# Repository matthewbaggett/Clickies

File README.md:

Clickies
========

Clickies - Whats the maximum fun you can have with a set of 1" square PCBs?

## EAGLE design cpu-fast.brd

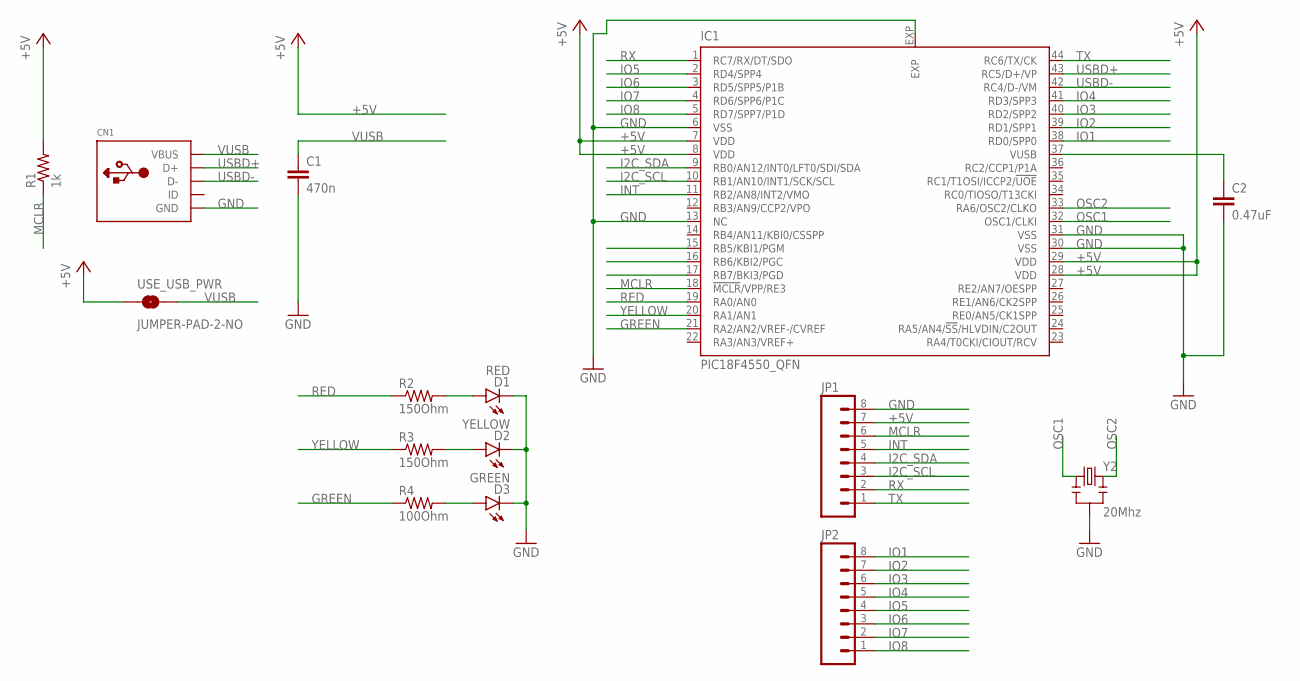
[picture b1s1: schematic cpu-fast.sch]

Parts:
C1: 470n; C0805K
C2: 0.47uF; 0603-CAP
CN1: USBMINIB; USB-MINIB
D1: RED; LED-0603
D2: YELLOW; LED-0603
D3: GREEN; LED-0603
IC1: PIC18F4550_QFN; QFN44ML8X8
JP1, JP2: M081X08; 1X08
R1: 1k; 0402-RES
R2, R3: 150Ohm; 0402-RES
R4: 100Ohm; 0402-RES
USE_USB_PWR: JUMPER-PAD-2-NO; PAD-JUMPER-2-NO_NO_SILK
Y2: 20Mhz; RESONATOR-SMD

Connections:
+5V: IC1.7 (VDD), IC1.8 (VDD), IC1.28 (VDD), IC1.29 (VDD), JP1.7, R1.2, USE_USB_PWR.1
GND: C1.2, C2.2, CN1.GND, D1.C, D2.C, D3.C, IC1.6 (VSS), IC1.13 (NC), IC1.30 (VSS), IC1.31 (VSS), IC1.EXP, JP1.8, Y2.2
GREEN: IC1.21 (RA2/AN2/VREF-/CVREF), R4.1
I2C_SCL: IC1.10 (RB1/AN10/INT1/SCK/SCL), JP1.3
I2C_SDA: IC1.9 (RB0/AN12/INT0/LFT0/SDI/SDA), JP1.4
INT: IC1.11 (RB2/AN8/INT2/VMO), JP1.5
IO1: IC1.38 (RD0/SPP0), JP2.8
IO2: IC1.39 (RD1/SPP1), JP2.7
IO3: IC1.40 (RD2/SPP2), JP2.6
IO4: IC1.41 (RD3/SPP3), JP2.5
IO5: IC1.2 (RD4/SPP4), JP2.4
IO6: IC1.3 (RD5/SPP5/P1B), JP2.3
IO7: IC1.4 (RD6/SPP6/P1C), JP2.2
IO8: IC1.5 (RD7/SPP7/P1D), JP2.1
MCLR: IC1.18 (!MCLR!/VPP/RE3), JP1.6, R1.1
unnamed: D1.A, R2.2
unnamed: D2.A, R3.2
unnamed: D3.A, R4.2
unnamed: C2.1, IC1.37 (VUSB)
OSC1: IC1.32 (OSC1/CLKI), Y2.1
OSC2: IC1.33 (RA6/OSC2/CLKO), Y2.3
RED: IC1.19 (RA0/AN0), R2.1
RX: IC1.1 (RC7/RX/DT/SDO), JP1.2
TX: IC1.44 (RC6/TX/CK), JP1.1
USBD+: CN1.D+, IC1.43 (RC5/D+/VP)
USBD-: CN1.D-, IC1.42 (RC4/D-/VM)
VUSB: C1.1, CN1.VBUS, USE_USB_PWR.2
YELLOW: IC1.20 (RA1/AN1), R3.1

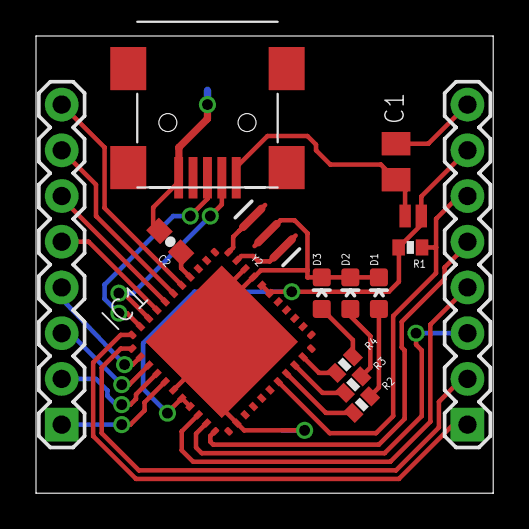
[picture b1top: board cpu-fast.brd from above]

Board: 2 copper layers, 25.4 x 25.4 mm, 15 parts (0 on the bottom side), 28 nets.

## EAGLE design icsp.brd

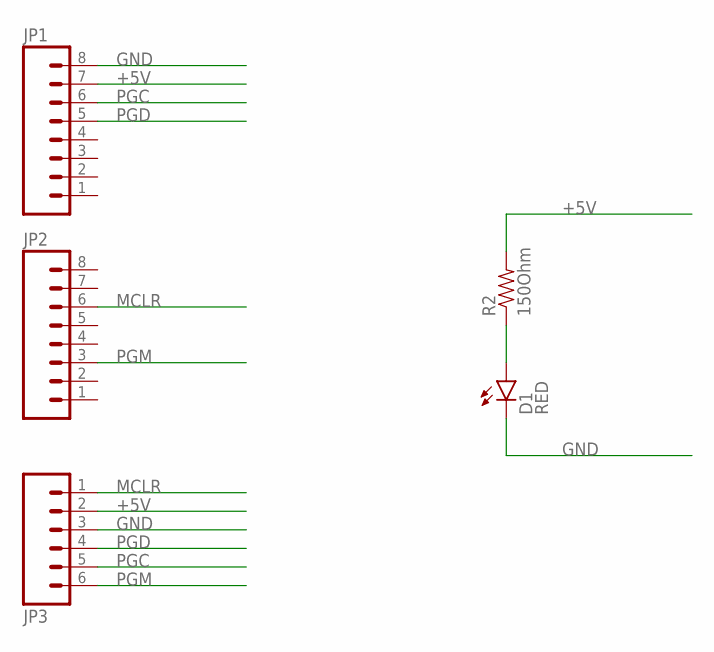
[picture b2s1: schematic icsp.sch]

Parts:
D1: RED; LED-0603
JP1, JP2: M081X08; 1X08
JP3: M06SIP_LOCK; 1X06-SIP_LOCK
R2: 150Ohm; 0402-RES

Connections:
+5V: JP1.7, JP3.2, R2.2
GND: D1.C, JP1.8, JP3.3
MCLR: JP2.6, JP3.1
unnamed: D1.A, R2.1
PGC: JP1.6, JP3.5
PGD: JP1.5, JP3.4
PGM: JP2.3, JP3.6

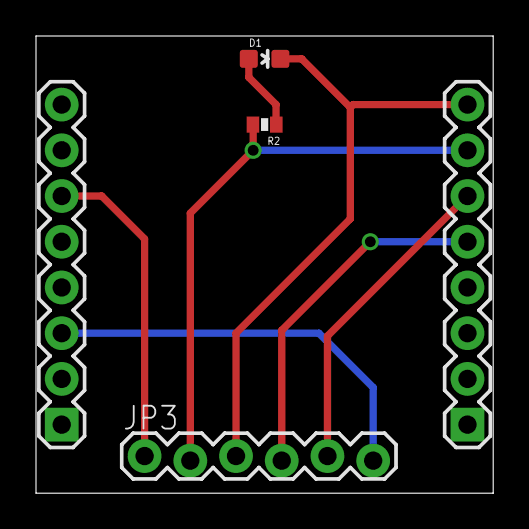
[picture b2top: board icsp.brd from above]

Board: 2 copper layers, 25.4 x 25.4 mm, 5 parts (0 on the bottom side), 7 nets.

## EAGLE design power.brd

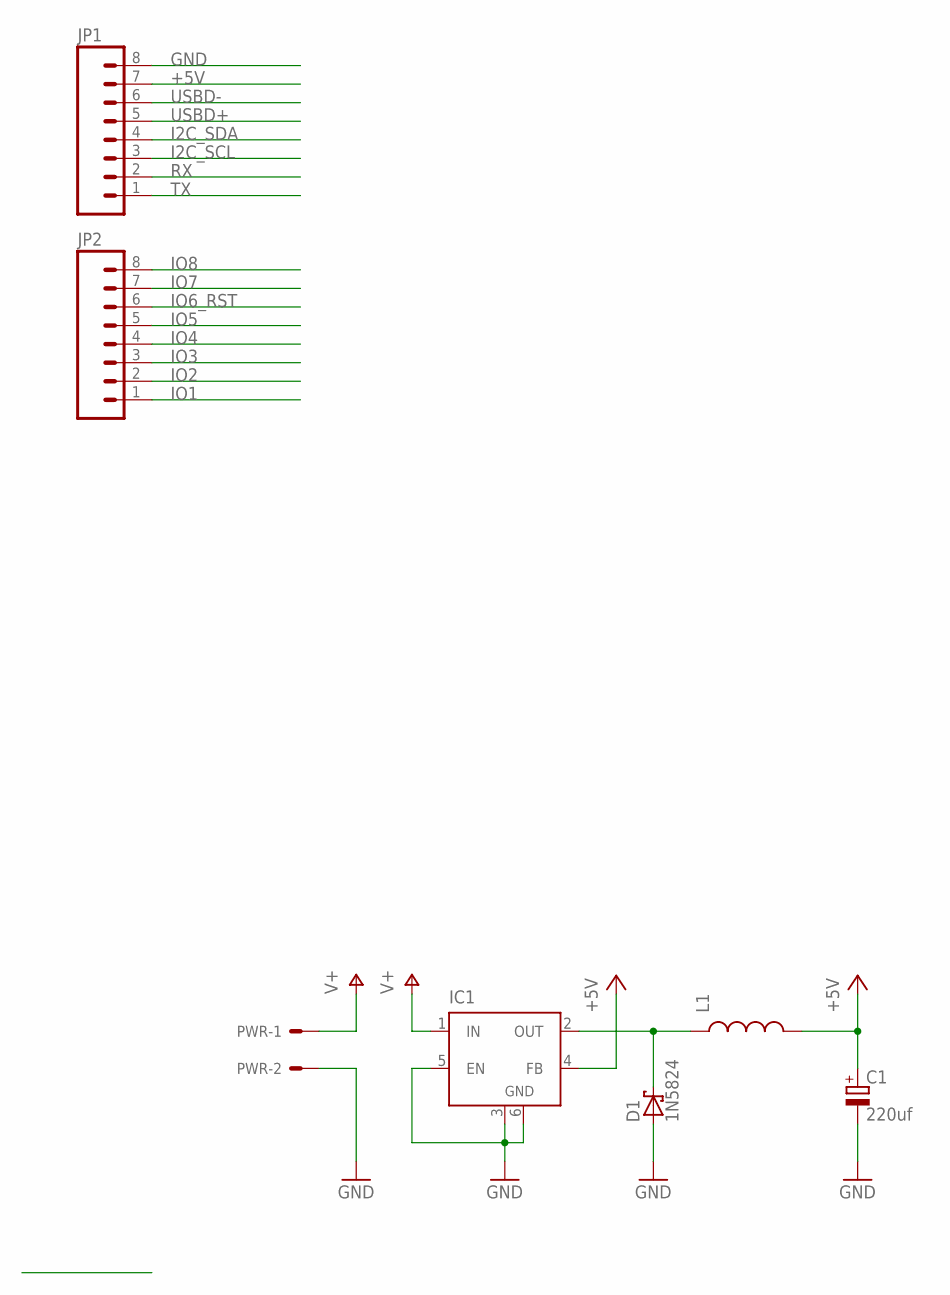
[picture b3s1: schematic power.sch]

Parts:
C1: 220uf; E2,5-6
D1: 1N5824; DO41-7.6
IC1: LM2596S; TO263-5
JP1, JP2: M081X08; 1X08
L1: INDUCTORSRU1038; SRU1038
PWR: 22-05-7028-02; 7395-02

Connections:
+5V: C1.+, IC1.4 (FB), JP1.7, L1.2
GND: C1.-, D1.A, IC1.3 (GND), IC1.5 (EN), IC1.6 (GND), JP1.8, PWR.2
I2C_SCL: JP1.3
I2C_SDA: JP1.4
IO1: JP2.1
IO2: JP2.2
IO3: JP2.3
IO4: JP2.4
IO5: JP2.5
IO6_RST: JP2.6
IO7: JP2.7
IO8: JP2.8
RX: JP1.2
TX: JP1.1
USBD+: JP1.5
USBD-: JP1.6
V+: IC1.1 (IN), PWR.1
VOUT: D1.C, IC1.2 (OUT), L1.1

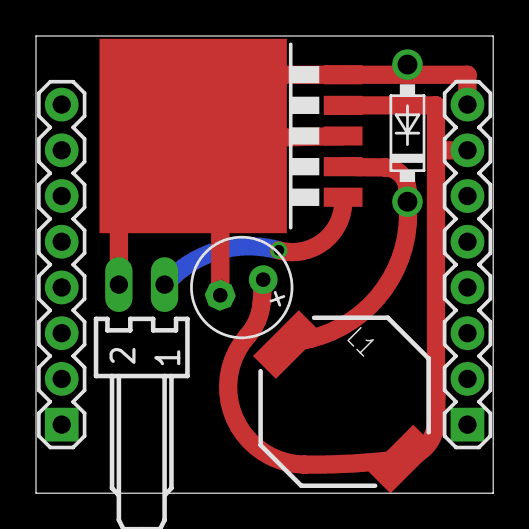
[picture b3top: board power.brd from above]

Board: 2 copper layers, 25.4 x 25.4 mm, 7 parts (0 on the bottom side), 4 nets.

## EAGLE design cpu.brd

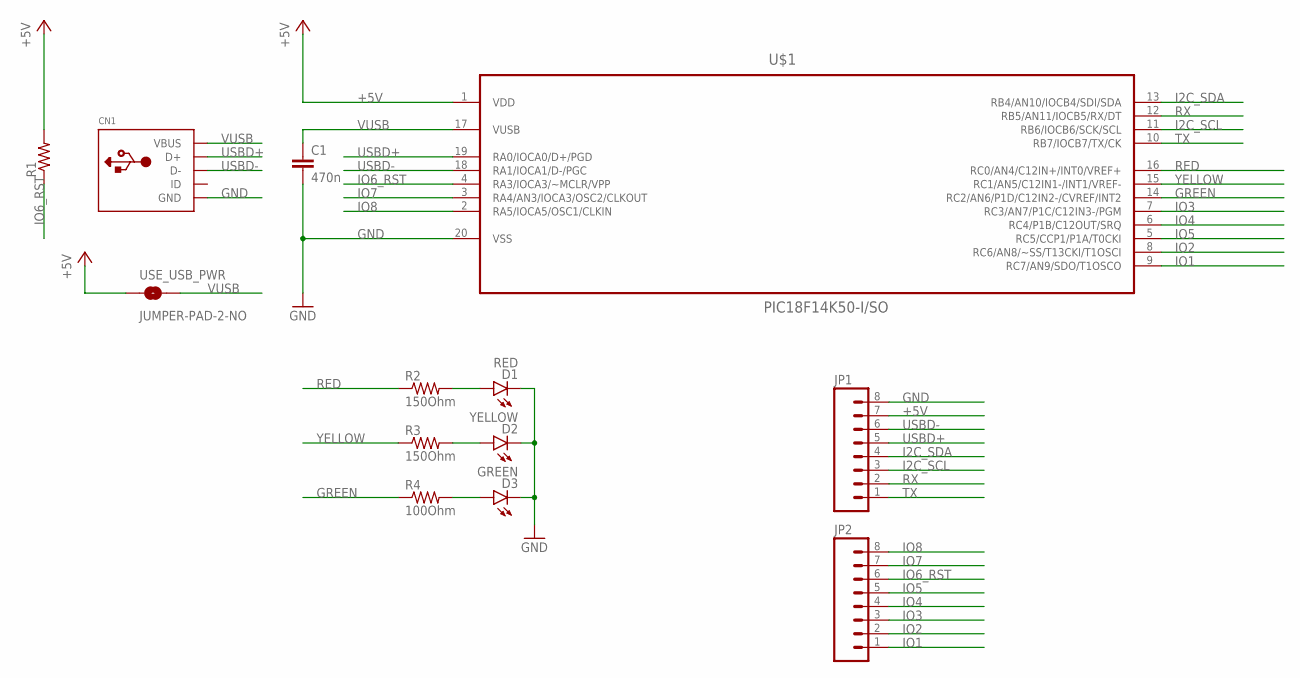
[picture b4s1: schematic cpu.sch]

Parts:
C1: 470n; C0805K
CN1: USBMINIB; USB-MINIB
D1: RED; LED-0603
D2: YELLOW; LED-0603
D3: GREEN; LED-0603
JP1, JP2: M081X08; 1X08
R1: RESISTOR0402-RES; 0402-RES
R2, R3: 150Ohm; 0402-RES
R4: 100Ohm; 0402-RES
U$1: PIC18F14K50-I/SO; SOIC127P1030X265-20N
USE_USB_PWR: JUMPER-PAD-2-NO; PAD-JUMPER-2-NO_NO_SILK

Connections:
+5V: JP1.7, R1.2, U$1.1 (VDD), USE_USB_PWR.1
GND: C1.2, CN1.GND, D1.C, D2.C, D3.C, JP1.8, U$1.20 (VSS)
GREEN: R4.1, U$1.14 (RC2/AN6/P1D/C12IN2-/CVREF/INT2)
I2C_SCL: JP1.3, U$1.11 (RB6/IOCB6/SCK/SCL)
I2C_SDA: JP1.4, U$1.13 (RB4/AN10/IOCB4/SDI/SDA)
IO1: JP2.1, U$1.9 (RC7/AN9/SDO/T1OSCO)
IO2: JP2.2, U$1.8 (RC6/AN8/~SS/T13CKI/T1OSCI)
IO3: JP2.3, U$1.7 (RC3/AN7/P1C/C12IN3-/PGM)
IO4: JP2.4, U$1.6 (RC4/P1B/C12OUT/SRQ)
IO5: JP2.5, U$1.5 (RC5/CCP1/P1A/T0CKI)
IO6_RST: JP2.6, R1.1, U$1.4 (RA3/IOCA3/~MCLR/VPP)
IO7: JP2.7, U$1.3 (RA4/AN3/IOCA3/OSC2/CLKOUT)
IO8: JP2.8, U$1.2 (RA5/IOCA5/OSC1/CLKIN)
unnamed: D1.A, R2.2
unnamed: D2.A, R3.2
unnamed: D3.A, R4.2
RED: R2.1, U$1.16 (RC0/AN4/C12IN+/INT0/VREF+)
RX: JP1.2, U$1.12 (RB5/AN11/IOCB5/RX/DT)
TX: JP1.1, U$1.10 (RB7/IOCB7/TX/CK)
USBD+: CN1.D+, JP1.5, U$1.19 (RA0/IOCA0/D+/PGD)
USBD-: CN1.D-, JP1.6, U$1.18 (RA1/IOCA1/D-/PGC)
VUSB: C1.1, CN1.VBUS, U$1.17 (VUSB), USE_USB_PWR.2
YELLOW: R3.1, U$1.15 (RC1/AN5/C12IN1-/INT1/VREF-)

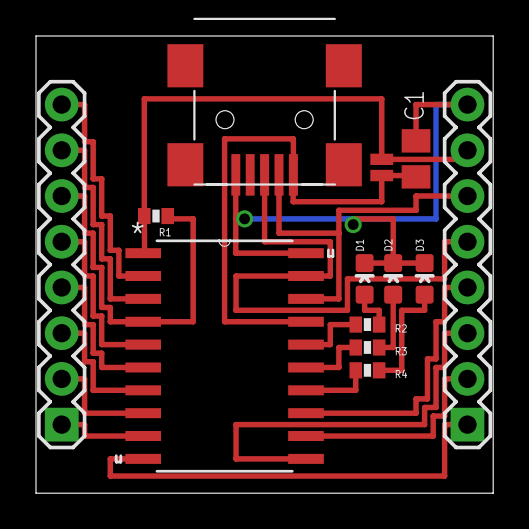
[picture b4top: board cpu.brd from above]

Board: 2 copper layers, 25.4 x 25.4 mm, 13 parts (0 on the bottom side), 23 nets.

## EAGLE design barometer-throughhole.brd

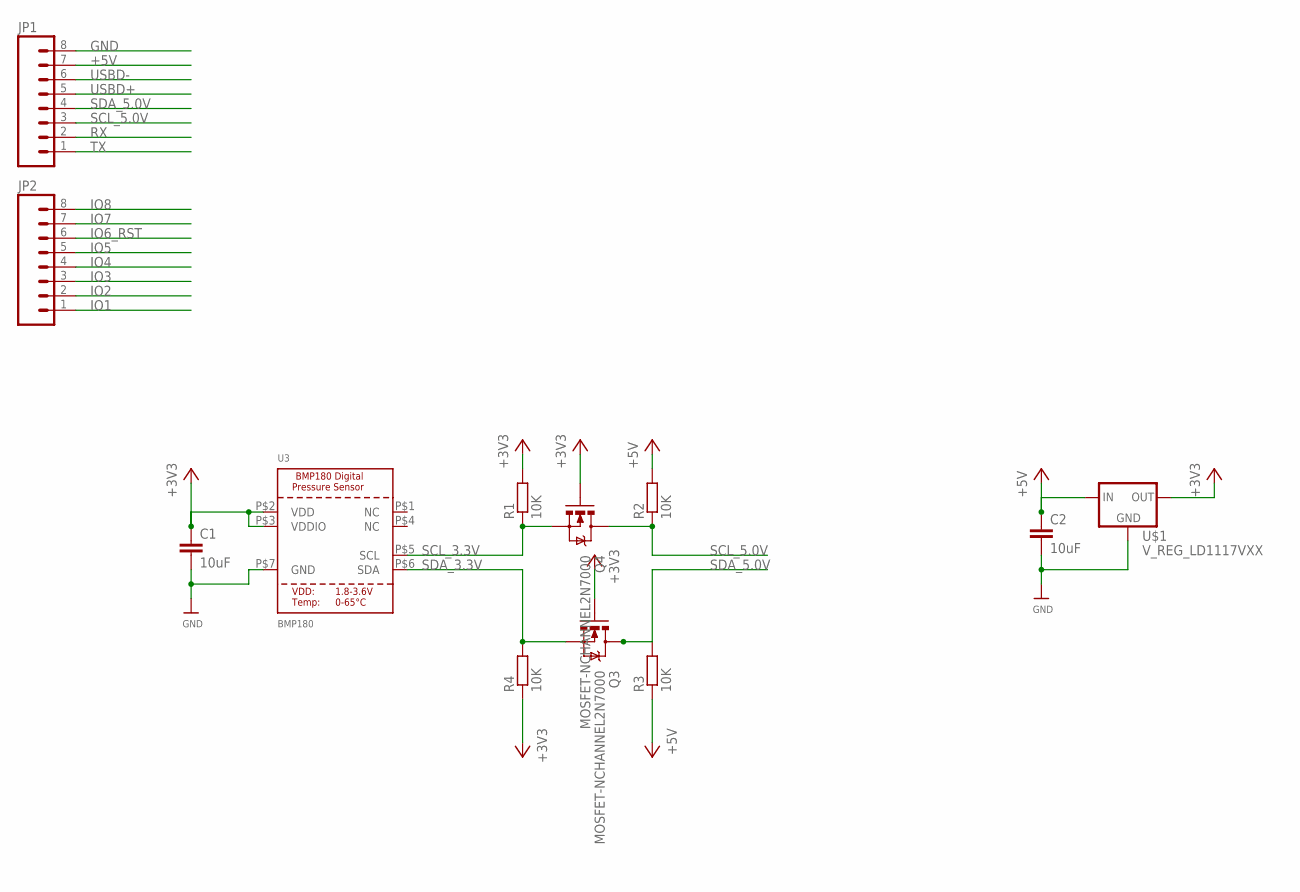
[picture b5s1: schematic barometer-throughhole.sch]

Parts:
C1, C2: 10uF; C025-030X050
JP1, JP2: M081X08; 1X08
Q3, Q4: MOSFET-NCHANNEL2N7000; TO-92
R1, R2, R3, R4: 10K; 0204/7
U3: BMP180; BMP180_EXTENDED
U$1: V_REG_LD1117VXX; 78XXL

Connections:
+3V3: C1.1, Q3.2 (G), Q4.2 (G), R1.2, R4.1, U3.P$2 (VDD), U3.P$3 (VDDIO), U$1.GND (OUT)
+5V: C2.1, JP1.7, R2.2, R3.1, U$1.OUT (IN)
GND: C1.2, C2.2, JP1.8, U3.P$7 (GND), U$1.IN (GND)
IO1: JP2.1
IO2: JP2.2
IO3: JP2.3
IO4: JP2.4
IO5: JP2.5
IO6_RST: JP2.6
IO7: JP2.7
IO8: JP2.8
RX: JP1.2
SCL_3.3V: Q4.1 (S), R1.1, U3.P$5 (SCL)
SCL_5.0V: JP1.3, Q4.3 (D), R2.1
SDA_3.3V: Q3.1 (S), R4.2, U3.P$6 (SDA)
SDA_5.0V: JP1.4, Q3.3 (D), R3.2
TX: JP1.1
USBD+: JP1.5
USBD-: JP1.6

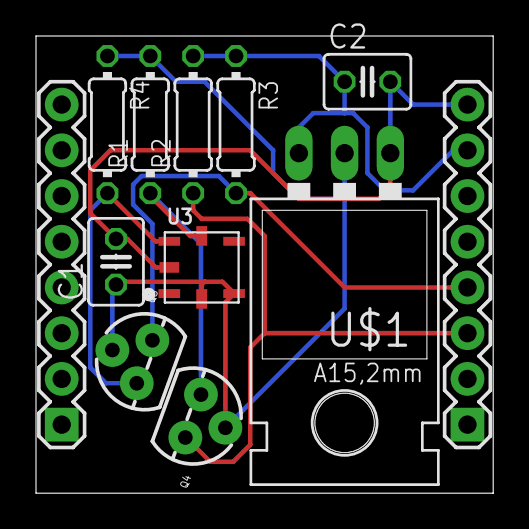
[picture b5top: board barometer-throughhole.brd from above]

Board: 2 copper layers, 25.4 x 25.4 mm, 12 parts (0 on the bottom side), 7 nets.

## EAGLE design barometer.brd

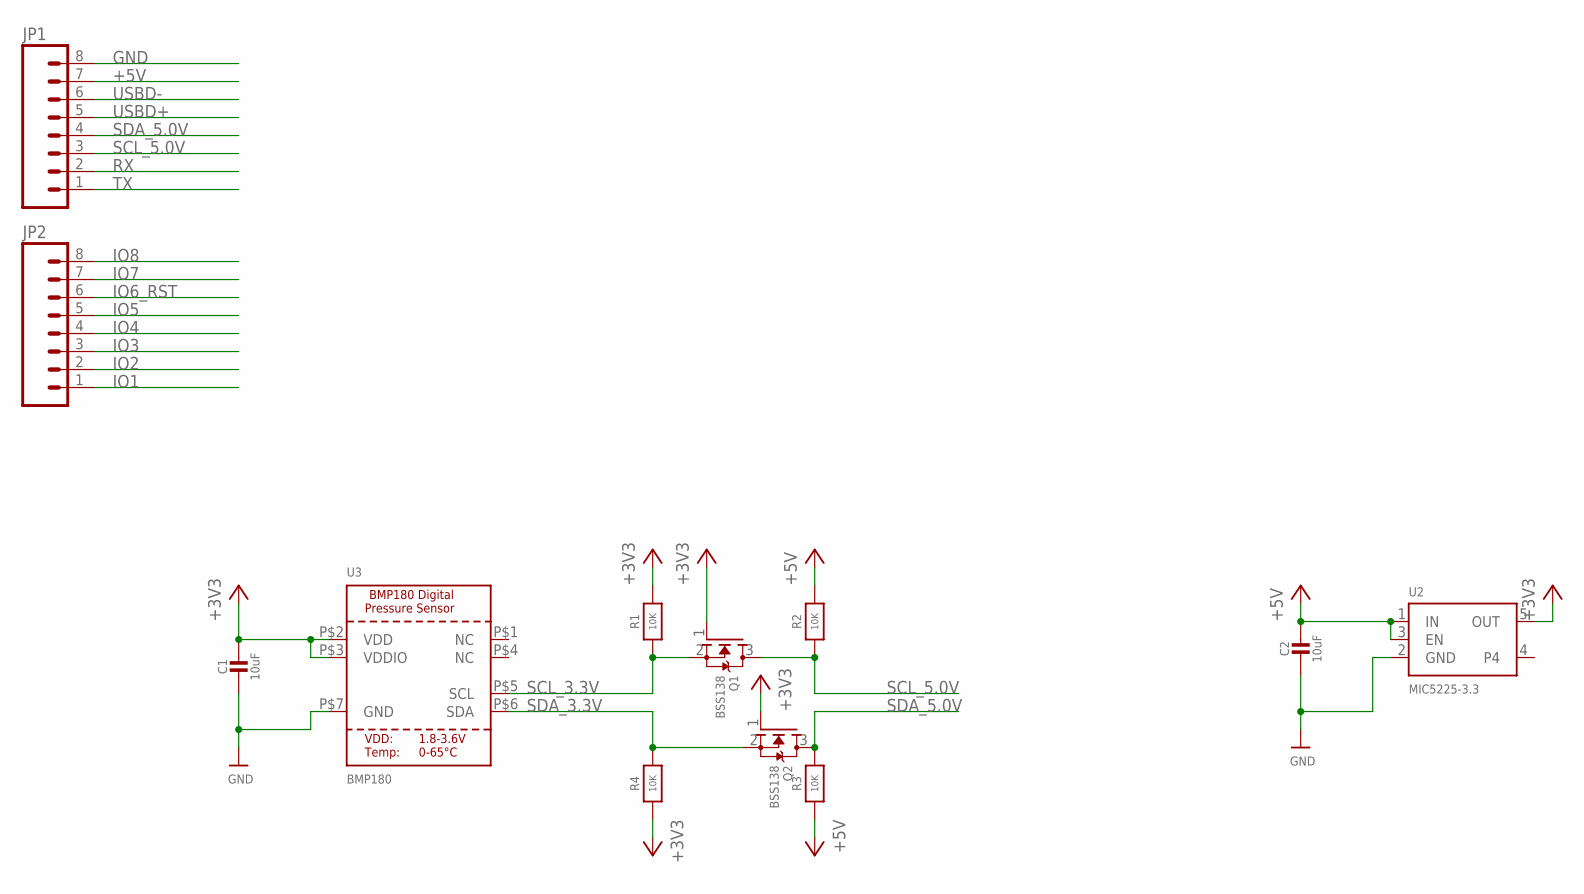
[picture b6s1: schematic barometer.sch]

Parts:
C1, C2: 10uF; 0805-NO
JP1, JP2: M081X08; 1X08
Q1, Q2: BSS138; SOT23
R1, R3, R4: 10K; 0805-NO
R2: 10K; _0805MP
U2: MIC5225-3.3; SOT23-5
U3: BMP180; BMP180_EXTENDED

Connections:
+3V3: C1.1, Q1.1 (G), Q2.1 (G), R1.2, R4.1, U2.5 (OUT), U3.P$2 (VDD), U3.P$3 (VDDIO)
+5V: C2.1, JP1.7, R2.2, R3.1, U2.1 (IN), U2.3 (EN)
GND: C1.2, C2.2, JP1.8, U2.2 (GND), U3.P$7 (GND)
IO1: JP2.1
IO2: JP2.2
IO3: JP2.3
IO4: JP2.4
IO5: JP2.5
IO6_RST: JP2.6
IO7: JP2.7
IO8: JP2.8
RX: JP1.2
SCL_3.3V: Q1.2 (S), R1.1, U3.P$5 (SCL)
SCL_5.0V: JP1.3, Q1.3 (D), R2.1
SDA_3.3V: Q2.2 (S), R4.2, U3.P$6 (SDA)
SDA_5.0V: JP1.4, Q2.3 (D), R3.2
TX: JP1.1
USBD+: JP1.5
USBD-: JP1.6

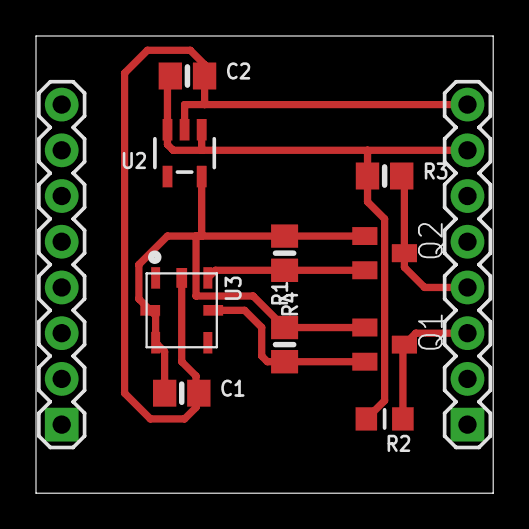
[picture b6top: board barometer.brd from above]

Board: 2 copper layers, 25.4 x 25.4 mm, 12 parts (0 on the bottom side), 7 nets.

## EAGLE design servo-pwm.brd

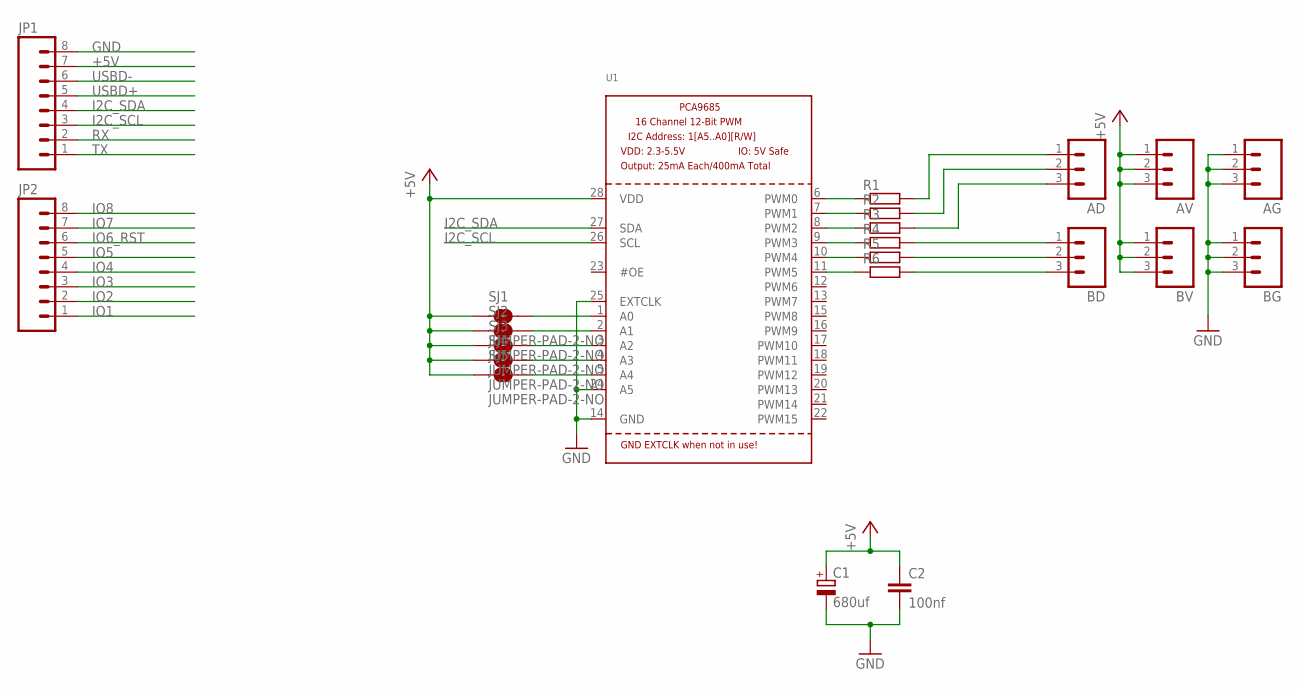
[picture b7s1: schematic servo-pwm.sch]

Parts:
AD: M03LOCK; 1X03_LOCK
AG: M03LOCK; 1X03_LOCK
AV: M03LOCK; 1X03_LOCK
BD: M03LOCK; 1X03_LOCK
BG: M03LOCK; 1X03_LOCK
BV: M03LOCK; 1X03_LOCK
C1: 680uf; E2,5-7
C2: 100nf; C025-030X050
JP1, JP2: M081X08; 1X08
R1, R2, R3, R4, R5, R6: R-EU_M0805; M0805
SJ1, SJ2, SJ3, SJ4, SJ5: JUMPER-PAD-2-NO; PAD-JUMPER-2-NO_NO_SILK
U1: PCA9685; TSSOP28

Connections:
+5V: AV.1, AV.2, AV.3, BV.1, BV.2, BV.3, C1.+, C2.1, JP1.7, SJ1.1, SJ2.1, SJ3.1, SJ4.1, SJ5.1, U1.28 (VDD)
GND: AG.1, AG.2, AG.3, BG.1, BG.2, BG.3, C1.-, C2.2, JP1.8, U1.14 (GND), U1.24 (A5), U1.25 (EXTCLK)
I2C_SCL: JP1.3, U1.26 (SCL)
I2C_SDA: JP1.4, U1.27 (SDA)
IO1: JP2.1
IO2: JP2.2
IO3: JP2.3
IO4: JP2.4
IO5: JP2.5
IO6_RST: JP2.6
IO7: JP2.7
IO8: JP2.8
unnamed: R4.1, U1.9 (PWM3)
unnamed: R5.1, U1.10 (PWM4)
unnamed: R6.1, U1.11 (PWM5)
unnamed: BD.3, R6.2
unnamed: AD.3, R3.2
unnamed: AD.2, R2.2
unnamed: AD.1, R1.2
unnamed: BD.2, R5.2
unnamed: BD.1, R4.2
unnamed: SJ1.2, U1.1 (A0)
unnamed: SJ2.2, U1.2 (A1)
unnamed: SJ5.2, U1.5 (A4)
unnamed: SJ3.2, U1.3 (A2)
unnamed: SJ4.2, U1.4 (A3)
unnamed: R3.1, U1.8 (PWM2)
unnamed: R2.1, U1.7 (PWM1)
unnamed: R1.1, U1.6 (PWM0)
RX: JP1.2
TX: JP1.1
USBD+: JP1.5
USBD-: JP1.6

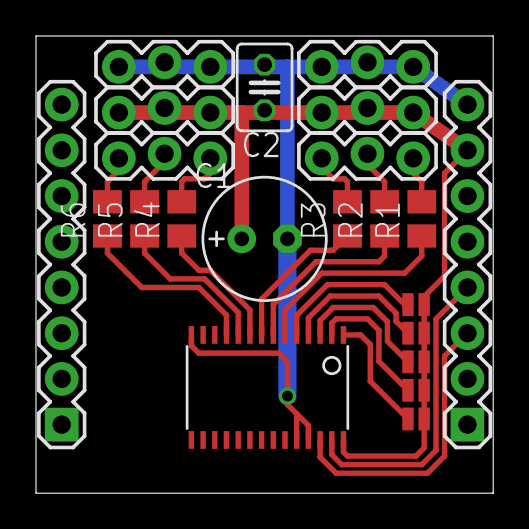
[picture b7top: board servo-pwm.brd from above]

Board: 2 copper layers, 25.4 x 25.4 mm, 22 parts (0 on the bottom side), 21 nets.

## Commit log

2014-09-07 Initial project with CPU board
2014-09-07 Adding blank template board.
2014-09-07 5V power control board mk1
2014-09-07 Tidy up schematic and part numbers
2014-09-07 Adding servo/pwm controller board
2014-09-13 Adding barometer board
2014-10-10 Rename barometer
2014-10-10 Barometer throughhole
2014-10-10 Deleted?
2014-10-10 Renamed bits on cpu
2014-10-10 Bits on power
2014-10-10 New ICSP header clickie
2014-10-10 updated eagle file
2014-10-11 CPU board using faster CPU for USB bootloader Needs finishing in terms of USB integration
2014-11-28 Changes I forgot to commit

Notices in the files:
parts and their libraries:
SparkFun-Connectors: Licensing: Creative Commons ShareAlike 4.0 International - https://creativecommons.org/licenses/by-sa/4.0
